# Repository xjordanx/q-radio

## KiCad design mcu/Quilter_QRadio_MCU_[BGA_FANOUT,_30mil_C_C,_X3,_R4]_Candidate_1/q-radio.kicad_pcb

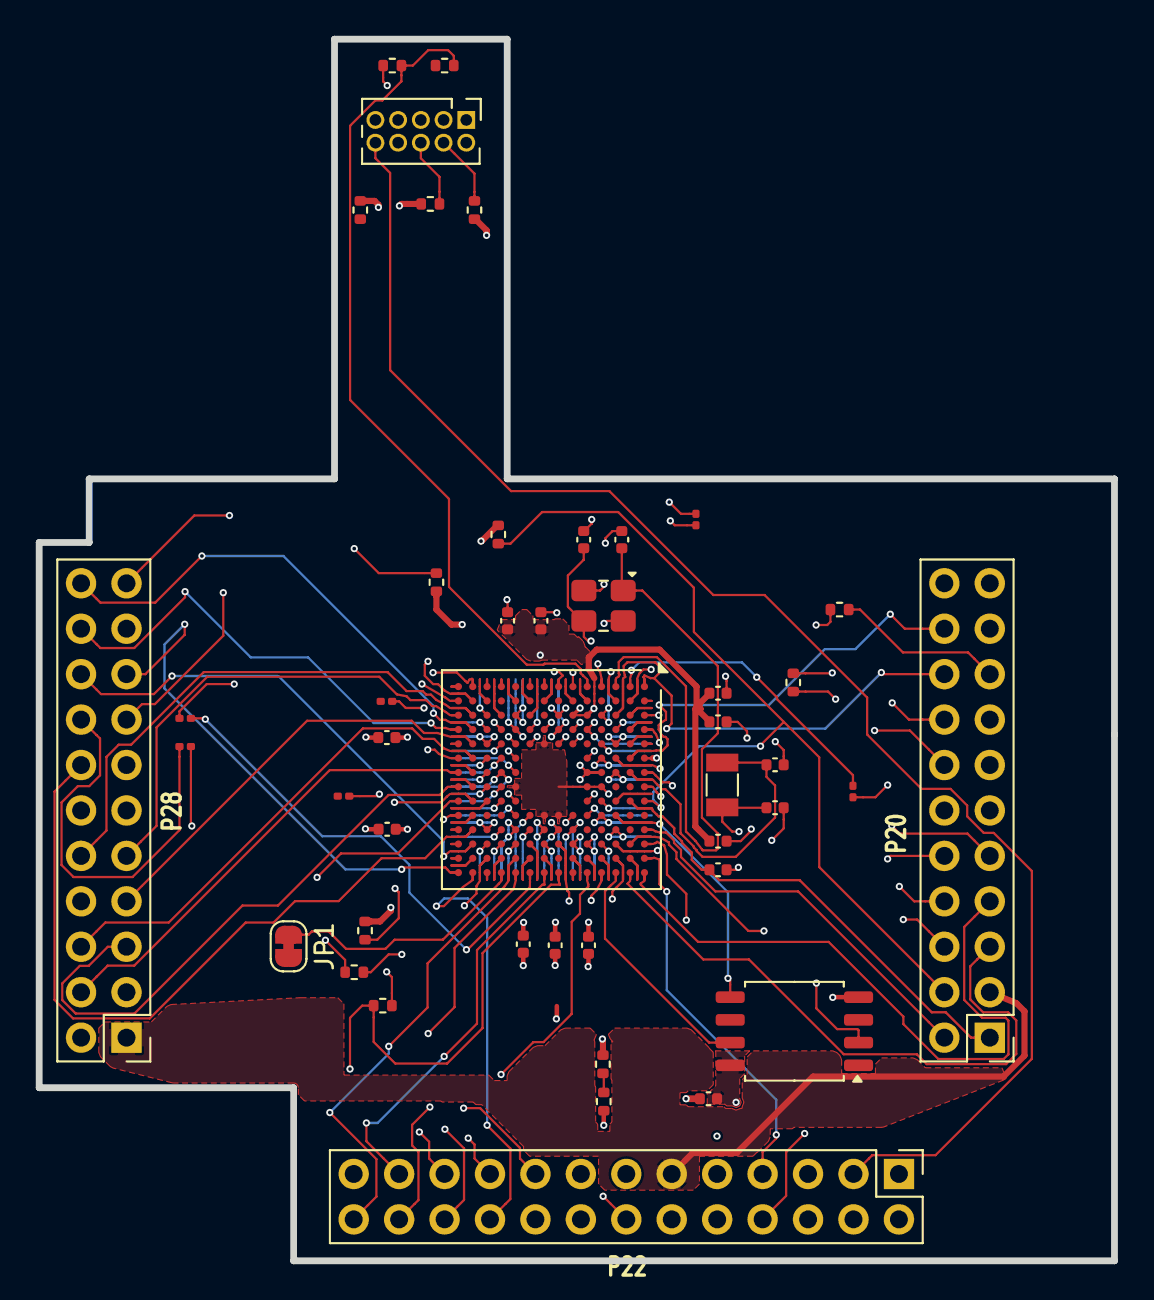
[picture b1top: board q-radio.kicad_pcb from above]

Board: 6 copper layers, 60.1 x 68.3 mm, 45 parts (0 on the bottom side), 85 nets.

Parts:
C118, C157, C158, C164: 18 pF; C_0402_1005Metric
C128, C129, C130, C131, C132, C133, C134, C135, C136, C137, C138, C144: 1 uF; C_0402_1005Metric
JP1: SolderJumper_2_Bridged; SolderJumper-2_P1.3mm_Bridged_RoundedPad1.0x1.5mm
P20, P28: HEADER_2x11; PinSocket_2x11_P2.54mm_Vertical_Flipped
P22: HEADER_2x13; PinSocket_2x13_P2.54mm_Vertical_Flipped
P26: LPC_JTAG; PinHeader_2x05_P1.27mm_Vertical
R6, R127, R140, R141: 100; R_0201_0603Metric
R37, R48, R59, R62, R63, R64, R66, R67, R68, R93: 10k; R_0402_1005Metric
R38: 180k; R_0402_1005Metric
R39: 37.4k; R_0402_1005Metric
R65, R82: 18k; R_0402_1005Metric
R69: 12k; R_0201_0603Metric
R107: 4.7k; R_0201_0603Metric
U20: W25Q32; SOIC-8_5.3x5.3mm_P1.27mm
U23: LPC4330FET180; TFBGA-180_12x12mm_Layout14x14_P0.8mm
X2: MCU_XTAL; Crystal_SMD_3225-4Pin_3.2x2.5mm
X3: RTC_XTAL; Crystal_SMD_3215-2Pin_3.2x1.5mm

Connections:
3V3AUX: P20.3, P22.11, P28.1
/Microcontroller/ADC0_0: P20.20, U23.B6 (ADC0_0/ADC1_0/DAC), U23.C5 (PB_6)
/Microcontroller/ADC0_2: P20.16, U23.B3 (ADC0_2/ADC1_2), U23.C2 (P4_5)
/Microcontroller/ADC0_3: R38.2, R39.1, U23.B4 (ADC0_3/ADC1_3)
/Microcontroller/ADC0_5: P20.18, U23.A1 (P4_4), U23.C3 (ADC0_5/ADC1_5)
/Microcontroller/ADC0_6: P20.14, U23.A4 (ADC0_6/ADC1_6), U23.D6 (PF_4)
/Microcontroller/CPLD_TCK: P28.17, U23.P14 (P6_1)
/Microcontroller/DBGEN: R64.1, U23.K4 (DBGEN)
/Microcontroller/GPIO3_8: P20.5, U23.B14 (P7_0)
/Microcontroller/GPIO3_9: P20.6, U23.C13 (P7_1)
/Microcontroller/GPIO3_10: P20.7, U23.A14 (P7_2)
/Microcontroller/GPIO3_11: P20.8, U23.C12 (P7_3)
/Microcontroller/GPIO3_12: P20.9, U23.C6 (P7_4)
/Microcontroller/GPIO3_13: P20.10, U23.A7 (P7_5)
/Microcontroller/GPIO3_14: P20.11, U23.F5 (P7_6)
/Microcontroller/GPIO3_15: P20.12, U23.D5 (P7_7)
/Microcontroller/I2C1_SCL: P22.5, U23.L9 (P2_4)
/Microcontroller/I2C1_SDA: P22.6, U23.G11 (P2_3)
/Microcontroller/I2S0_RX_SDA: P28.19, U23.K11 (P6_2)
/Microcontroller/I2S0_RX_WS: P22.15, U23.D10 (P3_1)
/Microcontroller/I2S0_TX_MCLK: P22.17, U23.P10 (CLK2)
/Microcontroller/I2S0_TX_SCK: P22.16, U23.D12 (P3_0)
/Microcontroller/I2S0_TX_SDA: P22.13, U23.D9 (P3_2)
/Microcontroller/ISP: R59.2, U23.G12 (P2_7)
/Microcontroller/P1_1: R67.1, U23.N1 (P1_1)
/Microcontroller/P1_2: R68.1, U23.N2 (P1_2)
/Microcontroller/P1_7: P28.22, U23.N4 (P1_7)
/Microcontroller/P2_8: P22.23, U23.H14 (P2_8)
/Microcontroller/P2_9: P22.21, R93.1, U23.G14 (P2_9)
/Microcontroller/P2_13: P22.22, U23.E14 (P2_13)
/Microcontroller/P5_3: P28.21, U23.P6 (P5_3)
/Microcontroller/P5_6: P28.13, U23.M11 (P5_6)
/Microcontroller/P5_7: P28.14, U23.N11 (P5_7)
/Microcontroller/P9_1: P28.20, U23.P4 (P9_1)
/Microcontroller/PA_3: P22.12, U23.E10 (PA_3)
/Microcontroller/PA_4: P22.9, U23.E12 (PA_4)
/Microcontroller/PB_0: P22.14, U23.D14 (PB_0)
/Microcontroller/PB_1: P22.7, U23.A13 (PB_1)
/Microcontroller/PB_3: P22.8, U23.A12 (PB_3)
/Microcontroller/PB_5: P20.2, U23.A11 (PB_5)
/Microcontroller/PE_0: P28.18, U23.N12 (PE_0)
/Microcontroller/RREF: R69.1, U23.G1 (USB0_RREF)
/Microcontroller/RTCX1: C118.1, U23.A8 (RTCX1), X3.2
/Microcontroller/RTCX2: C164.1, U23.B7 (RTCX2), X3.1
/Microcontroller/SD_CD: P28.3, U23.L8 (P1_13)
/Microcontroller/SD_CLK: P28.11, U23.M4 (CLK0)
/Microcontroller/SD_CMD: P28.9, U23.P3 (P1_6)
/Microcontroller/SD_DAT0: P28.7, U23.N5 (P1_9)
/Microcontroller/SD_DAT1: P28.6, U23.N6 (P1_10)
/Microcontroller/SD_DAT2: P28.5, U23.P8 (P1_11)
/Microcontroller/SD_DAT3: P28.4, U23.P7 (P1_12)
/Microcontroller/SD_POW: P28.10, U23.N3 (P1_5)
/Microcontroller/SD_VOLT0: P28.8, U23.M5 (P1_8)
/Microcontroller/SPIFI_CIPO: U20.2 (DO/IO_{1}), U23.B12 (P3_6)
/Microcontroller/SPIFI_COPI: U20.5 (DI/IO_{0}), U23.C10 (P3_7)
/Microcontroller/SPIFI_SCK: U20.6 (CLK), U23.B13 (P3_3)
/Microcontroller/SPIFI_SIO2: U20.3 (~WP/IO_{2}), U23.C11 (P3_5)
/Microcontroller/SPIFI_SIO3: U20.7 (~HOLD/~RESET/IO_{3}), U23.C14 (P3_4)
/Microcontroller/SPIFI_~CS: U20.1 (~CS), U23.C9 (P3_8)
/Microcontroller/TCK: P26.4, R66.2, U23.G5 (TCK/SWDCLK)
/Microcontroller/TDI: P26.8, U23.H4 (TDI)
/Microcontroller/TDO: P26.6, R63.1, U23.J5 (TDO/SWO)
/Microcontroller/TMS: P26.2, U23.K5 (TMS/SWDIO)
/Microcontroller/TRIGGER.IN: P28.16, R127.1
/Microcontroller/TRIGGER.OUT: P28.15, R6.2
/Microcontroller/U0_RXD: P22.19, U23.M13 (P2_1)
/Microcontroller/U0_TXD: P22.20, U23.N14 (P2_0)
/Microcontroller/USB0_VBUS: R62.1, R65.2, U23.E1 (USB0_VBUS)
/Microcontroller/VBAT: C136.1, P20.1, U23.B9 (VBAT)
/Microcontroller/VBUSCTRL: P20.17, R37.2
/Microcontroller/WAKEUP: P20.4, R48.2, U23.A9 (WAKEUP0)
/Microcontroller/XTAL1: C157.1, U23.C1 (XTAL1), X2.1
/Microcontroller/XTAL2: C158.1, U23.D1 (XTAL2), X2.3
/Microcontroller/~RESET: P22.3, P26.10, U23.C7 (~RESET)
GND: C118.2, C128.2, C129.2, C130.2, C131.2, C132.2, C133.2, C134.2, C135.2, C136.2, C137.2, C138.2, C144.2, C157.2, C158.2, C164.2, P20.13, P20.15, P20.19, P22.4, P22.10, P22.18, P26.3, P26.5, P26.9, P28.2, P28.12, R39.2, R65.1, R68.2, R69.2, R82.1, R93.2, R107.2, U20.4 (GND), U23.A3 (VSSA), U23.D7 (VSS), U23.E6 (VSS), U23.E7 (VSS), U23.E9 (VSS), U23.F1 (USB0_VSSA_REF), U23.F10 (VSS), U23.G3 (USB0_VSSA_TERM), U23.K6 (VSS), U23.K9 (VSS), X2.2, X2.4
unnamed: JP1.1 (A), U23.L14 (P6_5)
unnamed: R140.1, U23.P2 (P1_4)
unnamed: R141.1, U23.N9 (P1_19)
unnamed: R6.1, U23.J14 (P2_6)
unnamed: R37.1, R82.2, U23.B2 (P4_3)
unnamed: R107.1, U23.B1 (P4_6)
unnamed: R127.2, U23.P9 (PD_12)
SCL: P22.26, U23.K13 (I2C0_SCL)
SDA: P22.24, U23.K14 (I2C0_SDA)
VCC: C128.1, C129.1, C130.1, C131.1, C132.1, C133.1, C134.1, C135.1, C137.1, C138.1, C144.1, P26.1, R38.1, R48.1, R59.1, R63.2, R64.2, R66.1, R67.2, U20.8 (VCC), U23.A6 (VDDA), U23.D8 (VDDREG), U23.E3 (USB0_VDDA3V3_DRIVER), U23.E8 (VDDREG), U23.F3 (USB0_VDDA3V3), U23.G10 (VDDIO), U23.H5 (VDDIO), U23.H10 (VDDIO), U23.K8 (VDDIO)
